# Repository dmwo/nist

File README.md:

# nist
code and other things for nist

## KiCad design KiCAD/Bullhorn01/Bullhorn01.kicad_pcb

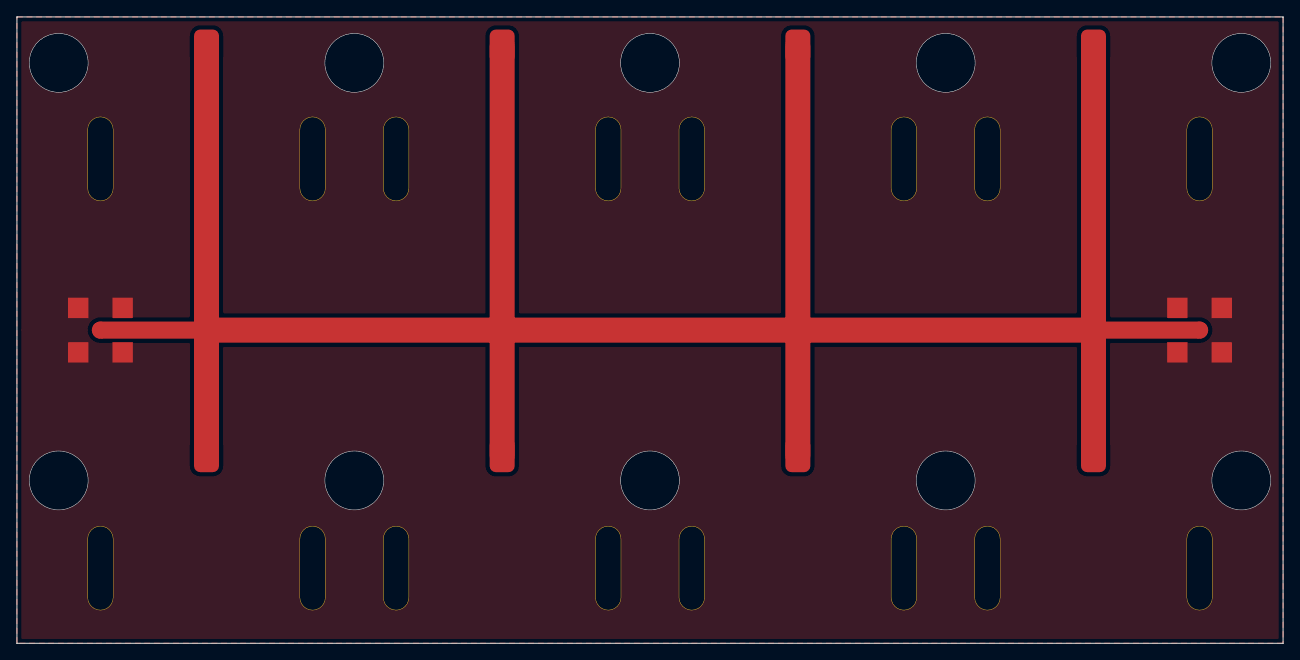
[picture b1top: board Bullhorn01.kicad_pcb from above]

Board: 2 copper layers, 151.6 x 75.0 mm, 10 parts (0 on the bottom side), 2 nets.

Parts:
H1, H2, H3, H4, H5, H6, H7, H8: ZX60-P103LN+
J1, J2: CONSMA001-SMD-G

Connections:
+5V: H1.2, H2.2, H3.2, H4.2, H5.2, H6.2, H7.2, H8.2, J1.1, J2.1
GND: H1.1, H2.1, H3.1, H4.1, H5.1, H6.1, H7.1, H8.1, J1.2, J2.2

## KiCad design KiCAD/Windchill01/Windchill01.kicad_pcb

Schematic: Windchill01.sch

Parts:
C1, C3: 10n; C_0402_1005Metric
C2, C4: 1u; C_0402_1005Metric
D1: LED; LED_0603_1608Metric
G1: Wind_Graphic; wind
J1, J2: C112640
J3: Battery_Holder; 1023
J4: 95278-101A14LF
Q1, Q2: MMBT3904; SOT-23
R1: 1.8k; R_0402_1005Metric
R2: 1M; R_0402_1005Metric
R3: 6.2M; R_0402_1005Metric
R4, R9, R11: 100k; R_0402_1005Metric
R5: 100; R_0402_1005Metric
R6: 10k; R_0402_1005Metric
R7: 499k; R_0402_1005Metric
R8: 180k; R_0402_1005Metric
R10: 80.6k; R_0402_1005Metric
R12: 332; R_0402_1005Metric
R13: 4.02k; R_0402_1005Metric
R14: 102k; R_0402_1005Metric
R15: 3.4k; R_0402_1005Metric
R16: 60.4k; R_0402_1005Metric
R17: 6.8k; R_0402_1005Metric
R18: 13.7k; R_0402_1005Metric
R19: 27.4k; R_0402_1005Metric
U1: AQY221R6V
U2: LTC6702; TSOT-23-8

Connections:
+INA: C4.1, J4.2, J4.4, J4.6, R16.1, U2.3 (+INA)
+INB: C3.1, R6.1, U2.5 (+INB)
-INA: Q2.2 (E), R3.2, R7.1, U2.2 (-INA)
-INB: R2.2, R15.2, R17.2, R18.2, R19.2, U2.6 (-INB)
/1ms: J4.1, R12.1
/10mV: J4.7, R15.1
/10ms: J4.3, R13.1
/20mV: J4.9, R17.1
/40mV: J4.11, R18.1
/80mV: J4.13, R19.1
/100ms: J4.5, R14.1
GND: C1.2, C2.1, C3.2, C4.2, D1.1, J1.2, J2.2, J3.4 (-), J4.8, J4.10, J4.12, J4.14, Q1.2 (E), R7.2, R9.1, R11.2, R16.2, U1.3, U2.4
unnamed: D1.2, R5.1
unnamed: J3.2 (-), J3.3 (+)
unnamed: Q1.1 (B), R4.1
unnamed: Q2.1 (B), R10.1, R11.1
OUTA: R4.2, R5.2, U2.1 (OUTA)
OUTB: R10.2, R12.2, R13.2, R14.2, U2.7 (OUTB)
RELAY+: R1.1, U1.1
RELAY-: Q1.3 (C), U1.2
VDD: C1.1, C2.2, J3.1 (+), R1.2, R2.1, R8.2, U2.8
Vdiv: Q2.3 (C), R3.1, R8.1, R9.2
sig: J1.1, J2.1, R6.2, U1.4

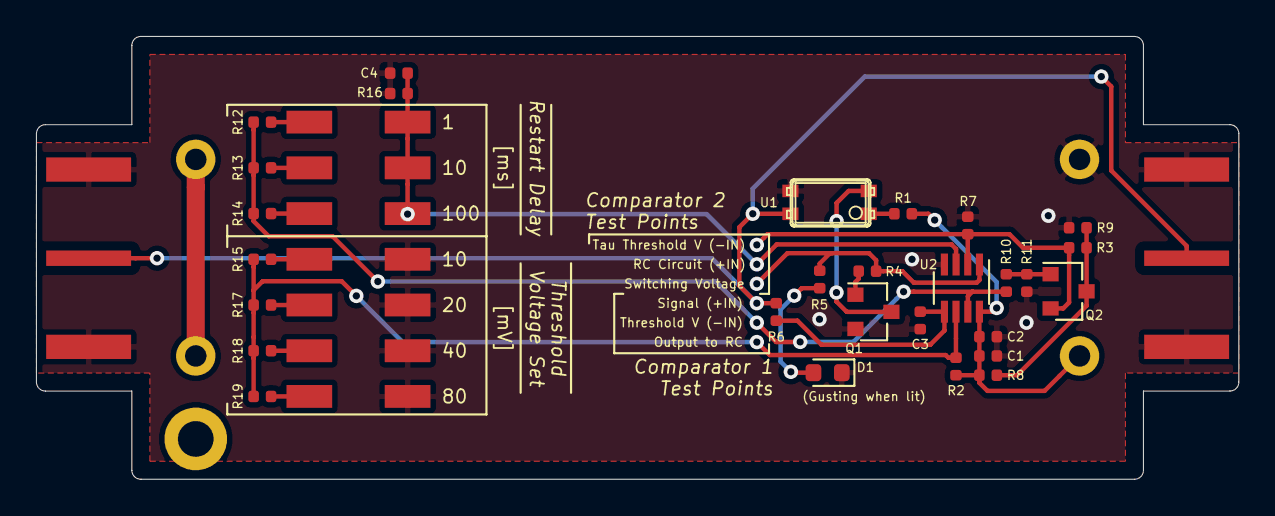
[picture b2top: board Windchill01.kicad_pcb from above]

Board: 2 copper layers, 66.8 x 24.6 mm, 33 parts (1 on the bottom side), 23 nets.

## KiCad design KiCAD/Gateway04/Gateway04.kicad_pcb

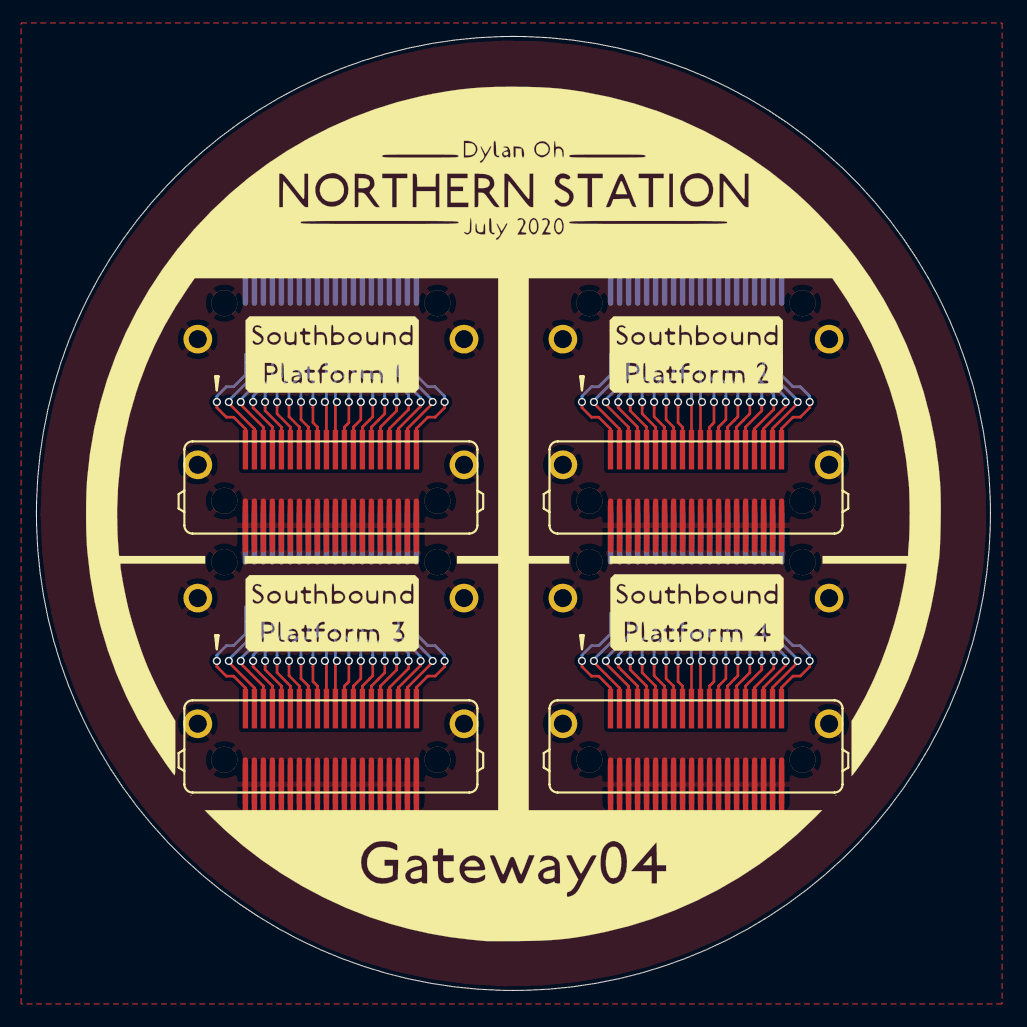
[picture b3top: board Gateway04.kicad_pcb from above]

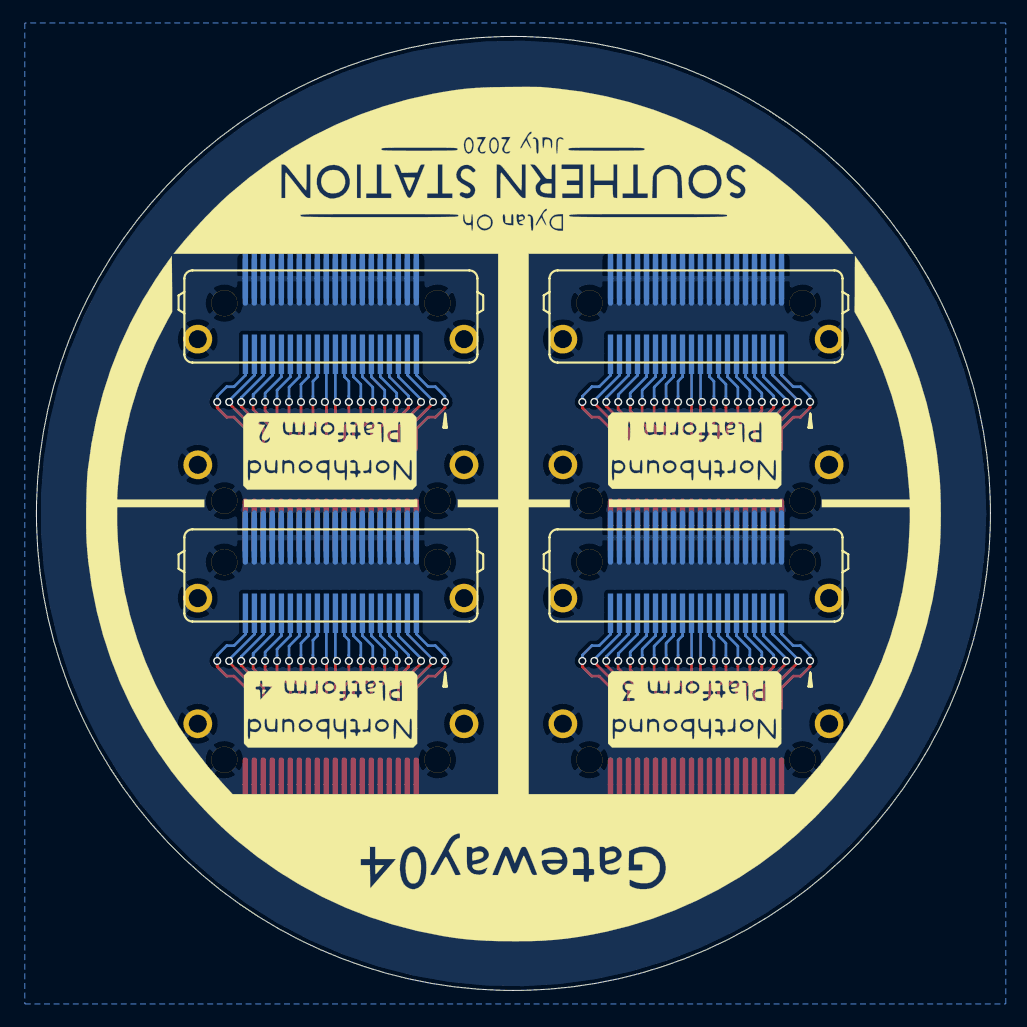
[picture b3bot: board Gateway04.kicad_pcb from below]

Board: 2 copper layers, 53.0 x 53.0 mm, 8 parts (4 on the bottom side), 81 nets.

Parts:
U1, U2, U3, U4, U5, U6, U7, U8: LSHM; LSHM-120-02.5-L-DV-A-S-TR

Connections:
GND: U1.0, U1.1, U1.3, U1.5, U1.7, U1.9, U1.11, U1.13, U1.15, U1.17, U1.19, U1.21, U1.23, U1.25, U1.27, U1.29, U1.31, U1.33, U1.35, U1.37, U1.39, U2.0, U2.1, U2.3, U2.5, U2.7, U2.9, U2.11, U2.13, U2.15, U2.17, U2.19, U2.21, U2.23, U2.25, U2.27, U2.29, U2.31, U2.33, U2.35, U2.37, U2.39, U3.0, U3.1, U3.3, U3.5, U3.7, U3.9, U3.11, U3.13, U3.15, U3.17, U3.19, U3.21, U3.23, U3.25, U3.27, U3.29, U3.31, U3.33, U3.35, U3.37, U3.39, U4.0, U4.1, U4.3, U4.5, U4.7, U4.9, U4.11, U4.13, U4.15, U4.17, U4.19, U4.21, U4.23, U4.25, U4.27, U4.29, U4.31, U4.33, U4.35, U4.37, U4.39, U5.0, U5.1, U5.3, U5.5, U5.7, U5.9, U5.11, U5.13, U5.15, U5.17, U5.19, U5.21, U5.23, U5.25, U5.27, U5.29, U5.31, U5.33, U5.35, U5.37, U5.39, U6.0, U6.1, U6.3, U6.5, U6.7, U6.9, U6.11, U6.13, U6.15, U6.17, U6.19, U6.21, U6.23, U6.25, U6.27, U6.29, U6.31, U6.33, U6.35, U6.37, U6.39, U7.0, U7.1, U7.3, U7.5, U7.7, U7.9, U7.11, U7.13, U7.15, U7.17, U7.19, U7.21, U7.23, U7.25, U7.27, U7.29, U7.31, U7.33, U7.35, U7.37, U7.39, U8.0, U8.1, U8.3, U8.5, U8.7, U8.9, U8.11, U8.13, U8.15, U8.17, U8.19, U8.21, U8.23, U8.25, U8.27, U8.29, U8.31, U8.33, U8.35, U8.37, U8.39
unnamed: U1.2, U2.2
unnamed: U1.4, U2.4
unnamed: U1.6, U2.6
unnamed: U1.8, U2.8
unnamed: U1.10, U2.10
unnamed: U1.12, U2.12
unnamed: U1.14, U2.14
unnamed: U1.16, U2.16
unnamed: U1.18, U2.18
unnamed: U1.20, U2.20
unnamed: U1.22, U2.22
unnamed: U1.24, U2.24
unnamed: U1.26, U2.26
unnamed: U1.28, U2.28
unnamed: U1.30, U2.30
unnamed: U1.32, U2.32
unnamed: U1.34, U2.34
unnamed: U1.36, U2.36
unnamed: U1.38, U2.38
unnamed: U1.40, U2.40
unnamed: U3.2, U4.2
unnamed: U3.4, U4.4
unnamed: U3.6, U4.6
unnamed: U3.8, U4.8
unnamed: U3.10, U4.10
unnamed: U3.12, U4.12
unnamed: U3.14, U4.14
unnamed: U3.16, U4.16
unnamed: U3.18, U4.18
unnamed: U3.20, U4.20
unnamed: U3.22, U4.22
unnamed: U3.24, U4.24
unnamed: U3.26, U4.26
unnamed: U3.28, U4.28
unnamed: U3.30, U4.30
unnamed: U3.32, U4.32
unnamed: U3.34, U4.34
unnamed: U3.36, U4.36
unnamed: U3.38, U4.38
unnamed: U3.40, U4.40
unnamed: U5.2, U6.2
unnamed: U5.4, U6.4
unnamed: U5.6, U6.6
unnamed: U5.8, U6.8
unnamed: U5.10, U6.10
unnamed: U5.12, U6.12
unnamed: U5.14, U6.14
unnamed: U5.16, U6.16
unnamed: U5.18, U6.18
unnamed: U5.20, U6.20
unnamed: U5.22, U6.22
unnamed: U5.24, U6.24
unnamed: U5.26, U6.26
unnamed: U5.28, U6.28
unnamed: U5.30, U6.30
unnamed: U5.32, U6.32
unnamed: U5.34, U6.34
unnamed: U5.36, U6.36
unnamed: U5.38, U6.38
unnamed: U5.40, U6.40
unnamed: U7.2, U8.2
unnamed: U7.4, U8.4
unnamed: U7.6, U8.6
unnamed: U7.8, U8.8
unnamed: U7.10, U8.10
unnamed: U7.12, U8.12
unnamed: U7.14, U8.14
unnamed: U7.16, U8.16
unnamed: U7.18, U8.18
unnamed: U7.20, U8.20
unnamed: U7.22, U8.22
unnamed: U7.24, U8.24
unnamed: U7.26, U8.26
unnamed: U7.28, U8.28
unnamed: U7.30, U8.30
unnamed: U7.32, U8.32
unnamed: U7.34, U8.34
unnamed: U7.36, U8.36
unnamed: U7.38, U8.38
unnamed: U7.40, U8.40

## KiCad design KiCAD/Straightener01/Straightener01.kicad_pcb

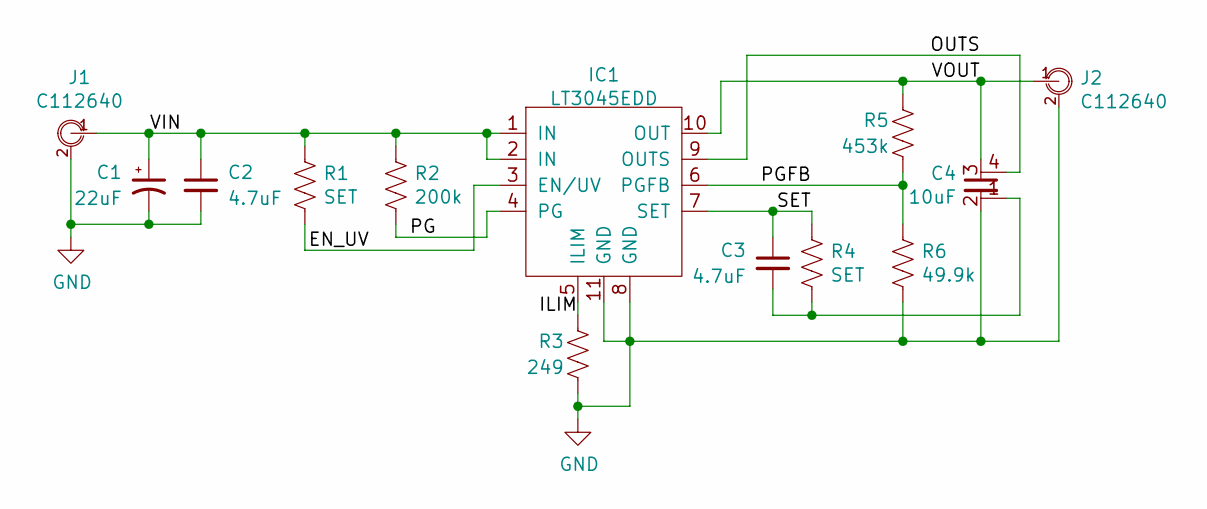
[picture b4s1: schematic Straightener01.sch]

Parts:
C1: 22uF; CP_Elec_5x5.3
C2, C3: 4.7uF; C_1206_3216Metric_Pad1.42x1.75mm_HandSolder
C4: 10uF; C_1206_Split
IC1: LT3045EDD; DFN-10
J1, J2: C112640
R1, R4: SET; R_0603_1608Metric_Pad1.05x0.95mm_HandSolder
R2: 200k; R_0603_1608Metric_Pad1.05x0.95mm_HandSolder
R3: 249; R_0603_1608Metric_Pad1.05x0.95mm_HandSolder
R5: 453k; R_0603_1608Metric_Pad1.05x0.95mm_HandSolder
R6: 49.9k; R_0603_1608Metric_Pad1.05x0.95mm_HandSolder

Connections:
/EN_UV: IC1.3 (EN/UV), R1.2
/ILIM: IC1.5 (ILIM), R3.1
/OUTS: C4.4, IC1.9 (OUTS)
/PG: IC1.4 (PG), R2.2
/PGFB: IC1.6 (PGFB), R5.2, R6.1
/SET: C3.1, IC1.7 (SET), R4.1
/VIN: C1.1, C2.1, IC1.1 (IN), IC1.2 (IN), J1.1, R1.1, R2.1
/VOUT: C4.3, IC1.10 (OUT), J2.1, R5.1
GND: C1.2, C2.2, C4.2, IC1.8 (GND), IC1.11 (GND), J1.2, J2.2, R3.2, R6.2
unnamed: C3.2, C4.1, R4.2

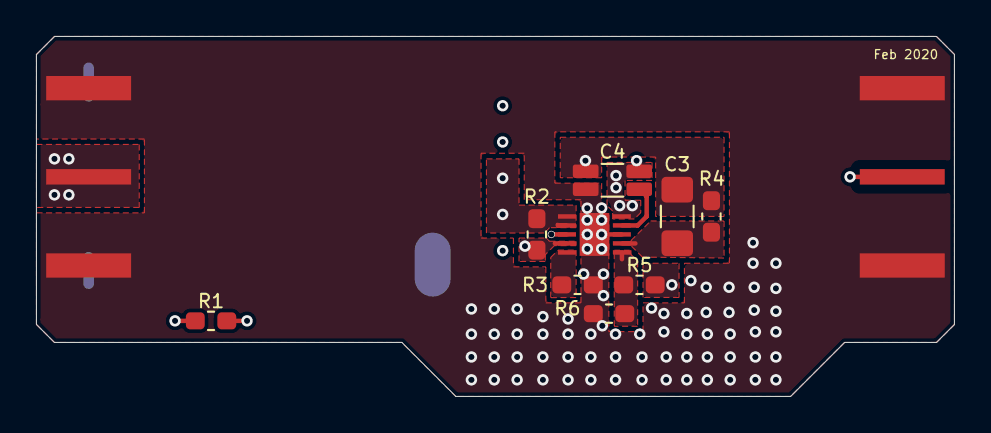
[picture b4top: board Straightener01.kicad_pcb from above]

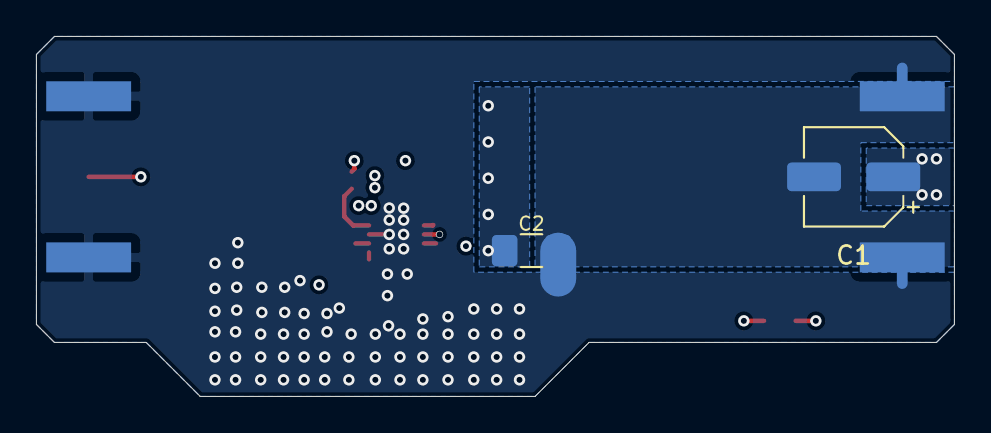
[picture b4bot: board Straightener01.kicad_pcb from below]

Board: 4 copper layers, 51.0 x 20.0 mm, 13 parts (2 on the bottom side), 10 nets.

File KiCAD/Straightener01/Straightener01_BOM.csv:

Item #,Ref Des,Qty,Cost/unit,Manufacturer,Mfg part #,Description,Package,Type,URL
1,C1,1,$0.35 ,Panasonic,EEE-1VA220WR,22uF Pol Cap,"Radial, Can",SMD,https://www.digikey.com/product-detail/en/panasonic-electron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
2,"C2, C3",2,$0.67 ,Murata,GCM31CR71E475KA55L,4.7uF,1206,SMD,https://www.digikey.com/product-detail/en/murata-electronics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
3,C4,1,$1.28 ,Murata,GJ831CR61E106KE83L,10uF,1206,SMD,https://www.digikey.com/product-detail/en/murata-electronics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
4,R2,1,$0.10 ,Vishay,CRCW0603200KJNEA,200 kOhm,0603,SMD,https://www.digikey.com/product-detail/en/vishay-dale/CRCW06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
5,R3,1,$0.10 ,Vishay,CRCW0603249RFKEA,249 Ohm,0603,SMD,https://www.digikey.com/product-detail/en/vishay-dale/CRCW06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
6,R5,1,$0.10 ,Vishay,CRCW0603453KFKEA,453 kOhm,0603,SMD,https://www.digikey.com/product-detail/en/vishay-dale/CRCW06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
7,R6,1,$0.10 ,Vishay,CRCW060349K9FKEA,49.9 kOhm,0603,SMD,https://www.digikey.com/product-detail/en/vishay-dale/CRCW06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
8,"J1, J2",2,$5.72 ,Amphenol,112640,BNC Jack,End Launch,SMD,https://www.digikey.com/product-detail/en/amphenol-rf/112640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
9,IC1,1,$6.78 ,Analog Devices,LT3045EDD#PBF,Regulator,10-DFN,SMD,https://www.digikey.com/product-detail/en/LT3045EDD%23PBF/LT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

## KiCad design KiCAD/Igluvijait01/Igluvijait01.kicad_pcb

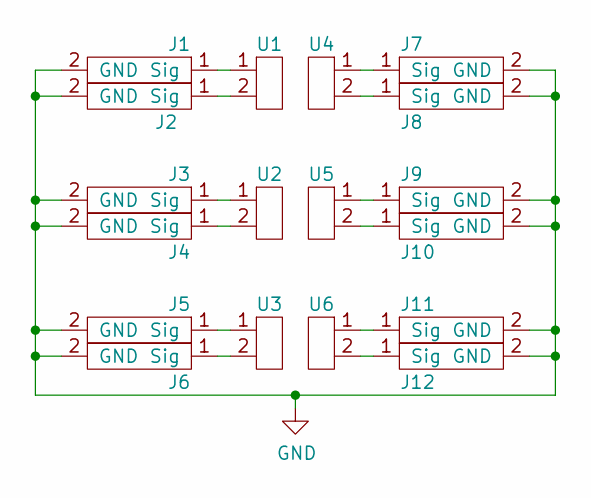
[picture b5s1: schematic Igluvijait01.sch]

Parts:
J1, J2, J3, J4, J5, J6, J7, J8, J9, J10, J11, J12: CONSMA001-SMD-G
U1, U2, U3, U4, U5, U6: TEST_PAD

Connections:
GND: J1.2 (GND), J2.2 (GND), J3.2 (GND), J4.2 (GND), J5.2 (GND), J6.2 (GND), J7.2 (GND), J8.2 (GND), J9.2 (GND), J10.2 (GND), J11.2 (GND), J12.2 (GND)
unnamed: J1.1 (Sig), U1.1
unnamed: J2.1 (Sig), U1.2
unnamed: J3.1 (Sig), U2.1
unnamed: J4.1 (Sig), U2.2
unnamed: J5.1 (Sig), U3.1
unnamed: J6.1 (Sig), U3.2
unnamed: J7.1 (Sig), U4.1
unnamed: J8.1 (Sig), U4.2
unnamed: J9.1 (Sig), U5.1
unnamed: J10.1 (Sig), U5.2
unnamed: J11.1 (Sig), U6.1
unnamed: J12.1 (Sig), U6.2

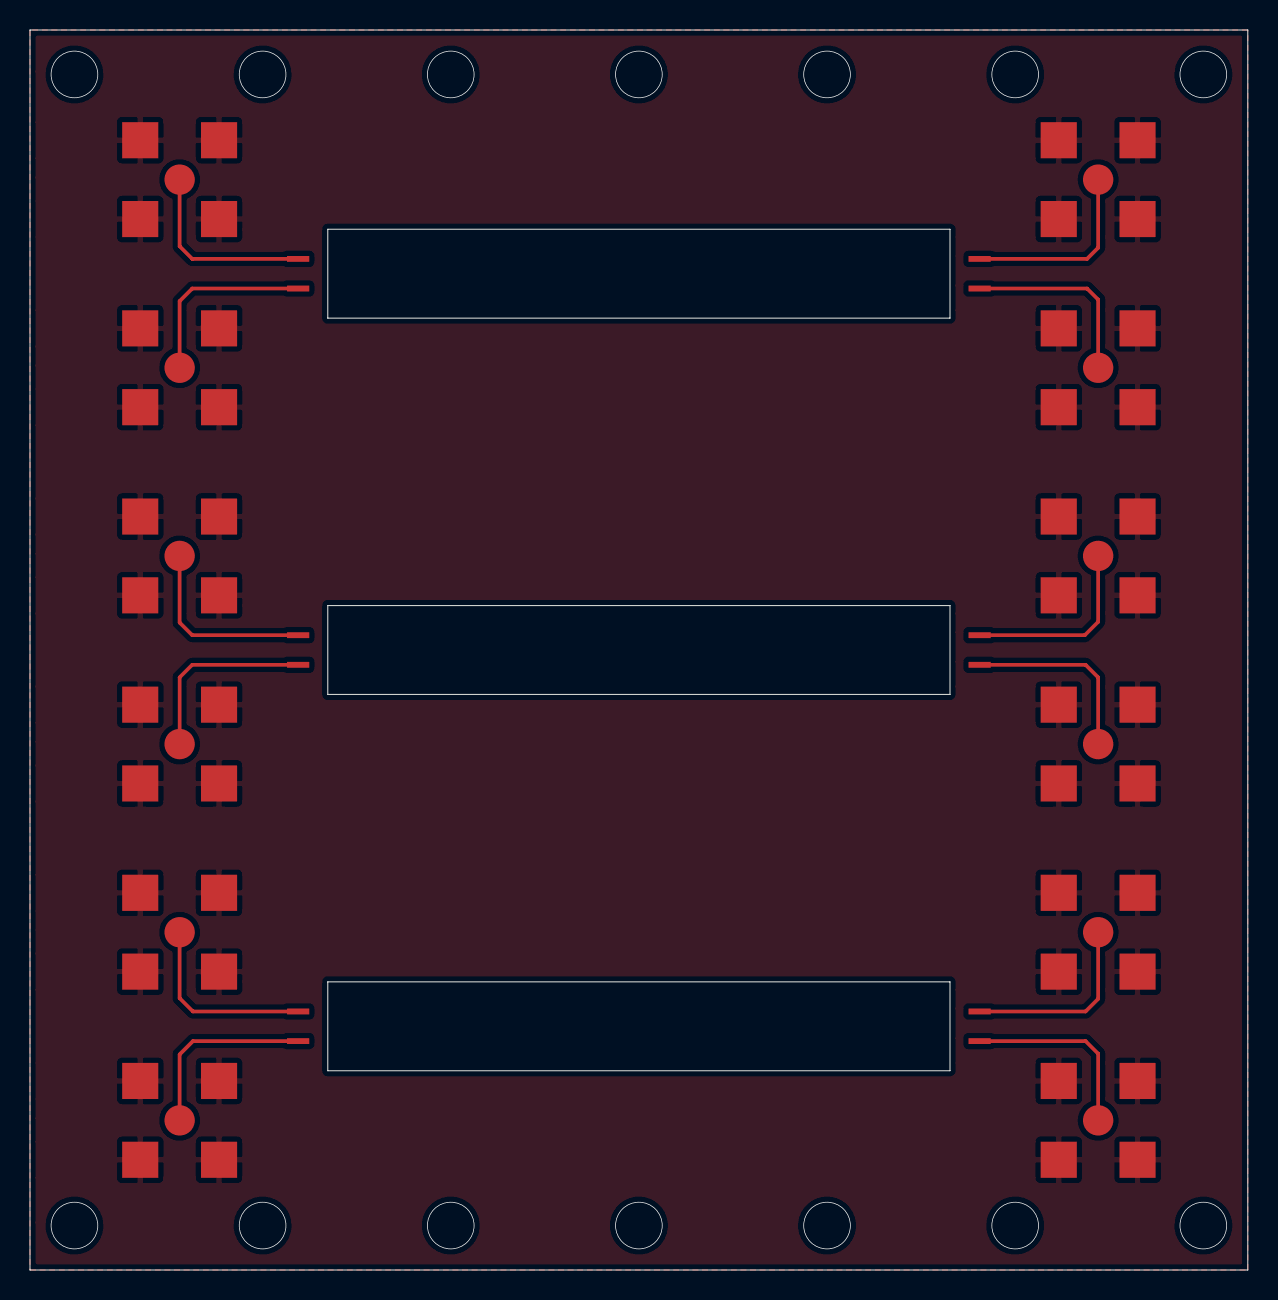
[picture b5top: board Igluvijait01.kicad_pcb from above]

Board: 2 copper layers, 82.2 x 83.7 mm, 18 parts (0 on the bottom side), 13 nets.

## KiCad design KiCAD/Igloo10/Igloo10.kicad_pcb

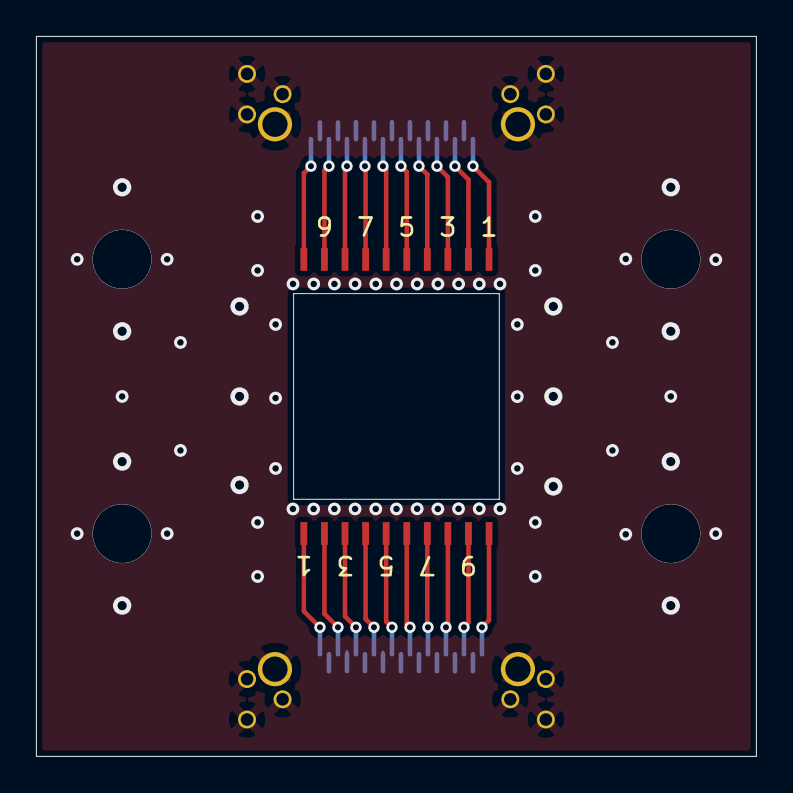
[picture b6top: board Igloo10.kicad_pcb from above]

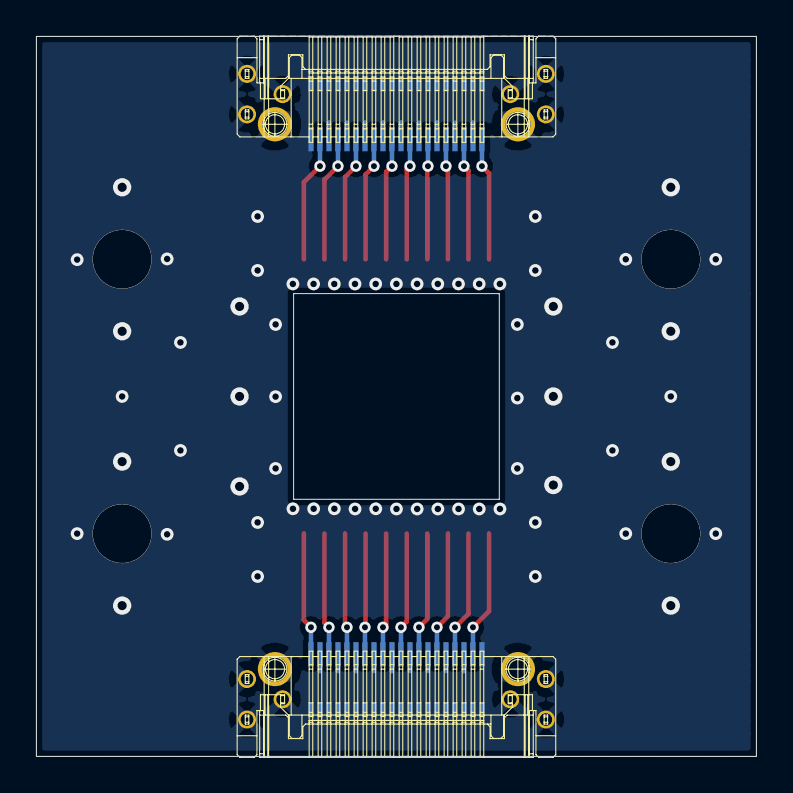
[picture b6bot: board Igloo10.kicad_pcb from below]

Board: 2 copper layers, 40.0 x 40.0 mm, 4 parts (2 on the bottom side), 21 nets.

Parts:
J1, J2: LSHM-120-01-L-RH-A-S-TR; LSHM-110-01-L-RH-A-S-TR
U1, U2: TEST_PAD

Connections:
GND: J1.1, J1.3, J1.4, J1.5, J1.7, J1.8, J1.9, J1.11, J1.12, J1.13, J1.15, J1.16, J1.17, J1.19, J1.20, J1.21, J1.23, J1.24, J1.25, J1.27, J1.28, J1.29, J1.31, J1.32, J1.33, J1.35, J1.36, J1.37, J1.39, J1.40, J1.41, J2.1, J2.3, J2.4, J2.5, J2.7, J2.8, J2.9, J2.11, J2.12, J2.13, J2.15, J2.16, J2.17, J2.19, J2.20, J2.21, J2.23, J2.24, J2.25, J2.27, J2.28, J2.29, J2.31, J2.32, J2.33, J2.35, J2.36, J2.37, J2.39, J2.40, J2.41
unnamed: J1.2, U1.10
unnamed: J1.6, U1.9
unnamed: J1.10, U1.8
unnamed: J1.14, U1.7
unnamed: J1.18, U1.6
unnamed: J1.22, U1.5
unnamed: J1.26, U1.4
unnamed: J1.30, U1.3
unnamed: J1.34, U1.2
unnamed: J1.38, U1.1
unnamed: J2.2, U2.10
unnamed: J2.6, U2.9
unnamed: J2.10, U2.8
unnamed: J2.14, U2.7
unnamed: J2.18, U2.6
unnamed: J2.22, U2.5
unnamed: J2.26, U2.4
unnamed: J2.30, U2.3
unnamed: J2.34, U2.2
unnamed: J2.38, U2.1

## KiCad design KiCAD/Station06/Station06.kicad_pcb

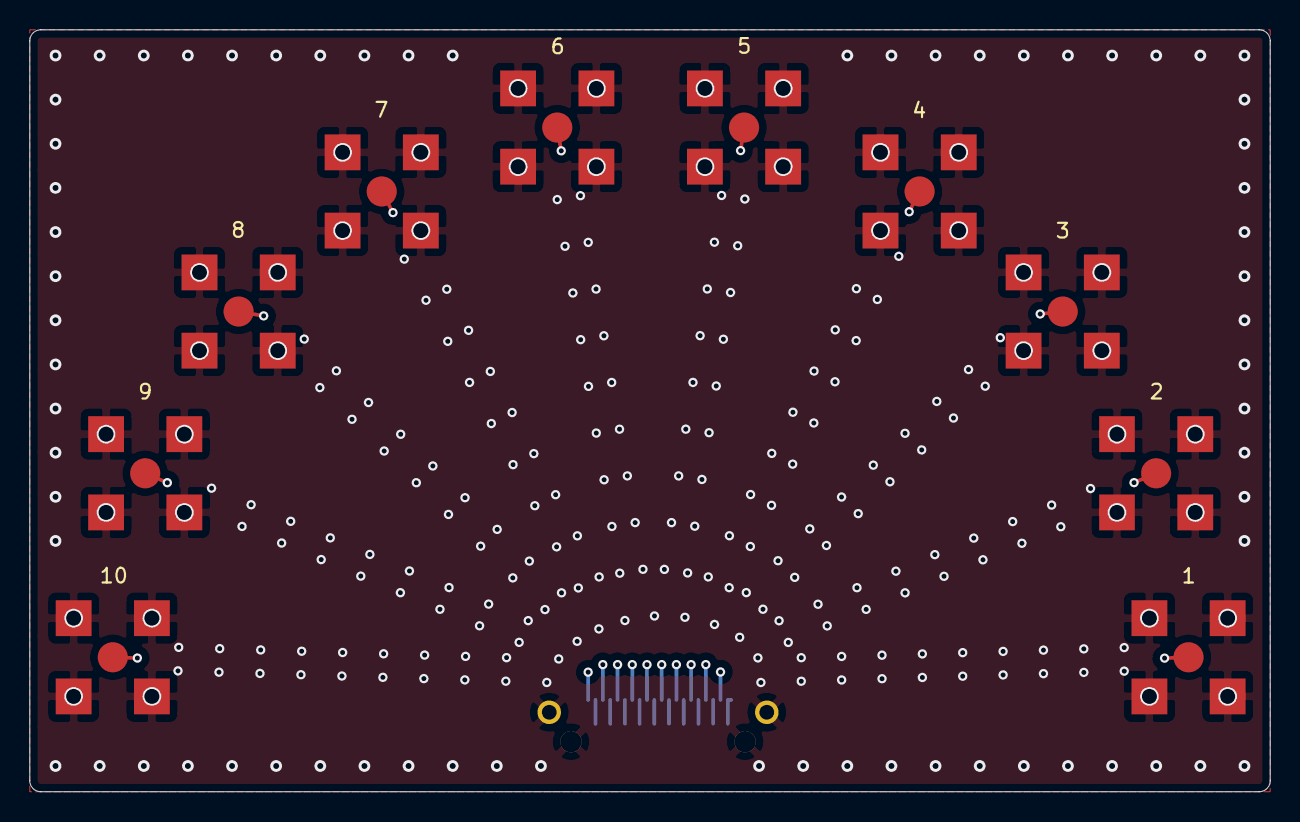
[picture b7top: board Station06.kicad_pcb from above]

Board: 4 copper layers, 84.3 x 51.8 mm, 11 parts (1 on the bottom side), 11 nets.

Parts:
J1: LSHM-120-02.5-L-DV-A-S-TR
J2, J3, J4, J5, J6, J7, J8, J9, J10, J11: CONSMA001-SMD-G

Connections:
GND: J1.0, J1.1, J1.3, J1.4, J1.5, J1.7, J1.8, J1.9, J1.11, J1.12, J1.13, J1.15, J1.16, J1.17, J1.19, J1.20, J1.21, J1.23, J1.24, J1.25, J1.27, J1.28, J1.29, J1.31, J1.32, J1.33, J1.35, J1.36, J1.37, J1.39, J1.40, J2.2, J3.2, J4.2, J5.2, J6.2, J7.2, J8.2, J9.2, J10.2, J11.2
unnamed: J1.2, J11.1
unnamed: J1.6, J10.1
unnamed: J1.10, J9.1
unnamed: J1.14, J8.1
unnamed: J1.18, J7.1
unnamed: J1.22, J6.1
unnamed: J1.26, J5.1
unnamed: J1.30, J4.1
unnamed: J1.34, J3.1
unnamed: J1.38, J2.1

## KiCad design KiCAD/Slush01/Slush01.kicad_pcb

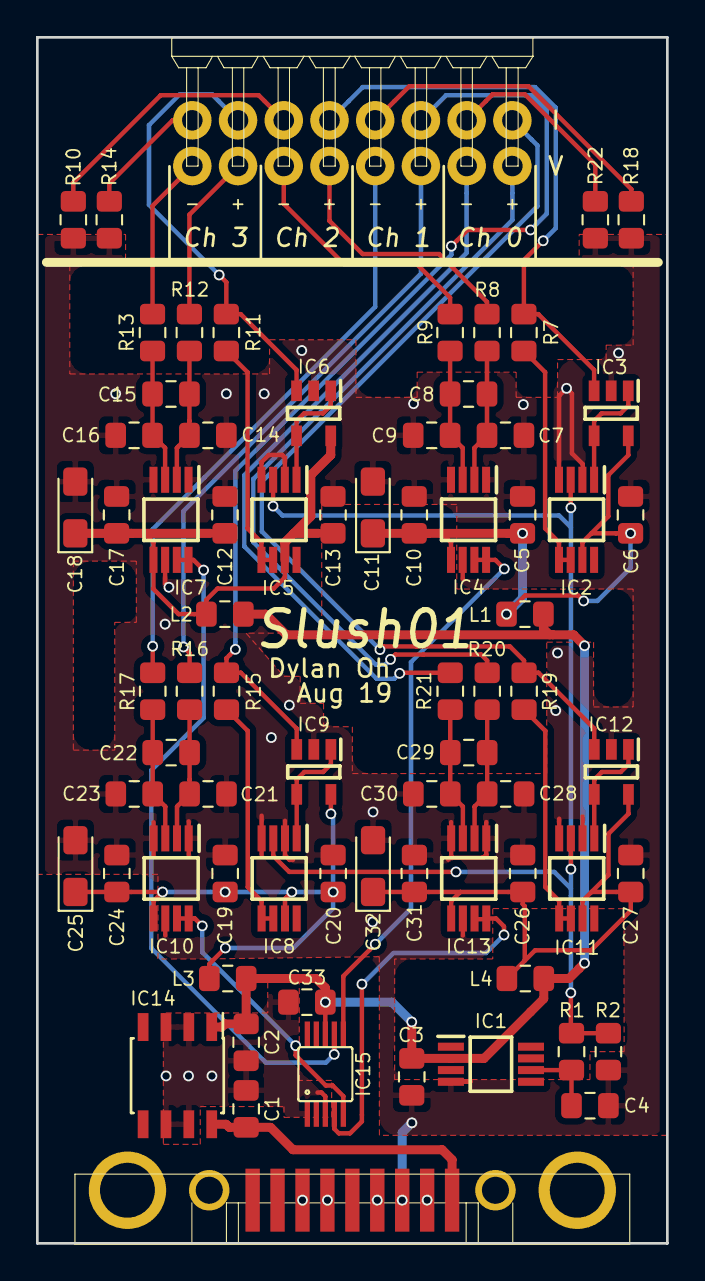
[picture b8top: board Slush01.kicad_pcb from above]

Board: 2 copper layers, 35.0 x 67.0 mm, 72 parts (0 on the bottom side), 48 nets.

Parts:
C1: 0.33uF; C_0805_2012Metric_Pad1.15x1.40mm_HandSolder
C2: 0.01uF; C_0805_2012Metric_Pad1.15x1.40mm_HandSolder
C3, C4, C5, C6, C7, C9, C10, C12, C13, C14, C16, C17, C19, C20, C21, C23, C24, C26, C27, C28, C30, C31, C33: 0.1uF; C_0805_2012Metric_Pad1.15x1.40mm_HandSolder
C8, C15, C22, C29: 1uF 6.3V X7R 0805; C_0805_2012Metric_Pad1.15x1.40mm_HandSolder
C11, C18, C25, C32: 10uF; CP_EIA-3216-18_Kemet-A_Pad1.58x1.35mm_HandSolder
IC1: ADR440ARMZ; MSOP-8
IC2, IC5, IC8, IC11: AD8276ARMZ; MSOP-8
IC3, IC6, IC9, IC12: AD8603AUJZ-R2; TSOT-23-5
IC4, IC7, IC10, IC13: AD8237ARMZ; MSOP-8
IC14: LM78L05; SOIC-8
IC15: ADS1115; VSSOP-10
J1: DB9F; K202XHT-E9S-N
J2: 90122-0128
L1, L2, L3, L4: MMZ2012Y152B; L_0805_2012Metric_Pad1.15x1.40mm_HandSolder
R1: 1050; R_0805_2012Metric_Pad1.15x1.40mm_HandSolder
R2: 1K; R_0805_2012Metric_Pad1.15x1.40mm_HandSolder
R7, R8, R9, R11, R12, R13, R15, R16, R17, R19, R20, R21: 100k; R_0805_2012Metric_Pad1.15x1.40mm_HandSolder
R10, R14, R18, R22: 10k; R_0805_2012Metric_Pad1.15x1.40mm_HandSolder

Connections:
/1V: IC2.3, IC5.3, IC8.3, IC11.3, R1.2, R2.1
/Channel0/I+: IC12.3, J2.2, R19.2
/Channel0/I-: J2.4, R22.1
/Channel0/V+: J2.1, R20.2
/Channel0/V-: J2.3, R21.2
/Channel0/Vpower: C26.1, C27.1, C31.1, C32.1, IC11.7, IC12.5, IC13.5, L4.2
/Channel0/out: IC13.7, IC13.8, IC15.4
/Channel1/I+: IC9.3, J2.6, R15.2
/Channel1/I-: J2.8, R18.1
/Channel1/V+: J2.5, R16.2
/Channel1/V-: J2.7, R17.2
/Channel1/Vpower: C19.1, C20.1, C24.1, C25.1, IC8.7, IC9.5, IC10.5, L3.2
/Channel1/out: IC10.7, IC10.8, IC15.5
/Channel2/I+: IC3.3, J2.10, R7.2
/Channel2/I-: J2.12, R10.1
/Channel2/V+: J2.9, R8.2
/Channel2/V-: J2.11, R9.2
/Channel2/Vpower: C5.1, C6.1, C10.1, C11.1, IC2.7, IC3.5, IC4.5, L1.2
/Channel2/out: IC4.7, IC4.8, IC15.6
/Channel3/I+: IC6.3, J2.14, R11.2
/Channel3/I-: J2.16, R14.1
/Channel3/V+: J2.13, R12.2
/Channel3/V-: J2.15, R13.2
/Channel3/Vpower: C12.1, C13.1, C17.1, C18.1, IC5.7, IC6.5, IC7.5, L2.2
/Channel3/out: IC7.7, IC7.8, IC15.7
/Power: C2.1, C3.1, C33.2, IC1.2, IC14.1, IC15.8, L1.1, L2.1, L3.1, L4.1
GND: C1.2, C2.2, C33.1, IC14.2, IC14.3, IC14.6, IC14.7, IC15.1, IC15.3, J1.2, J1.7, J1.8, J1.9, J1.10
GNDA: C3.2, C4.2, C5.2, C6.2, C7.1, C9.2, C10.2, C11.2, C12.2, C13.2, C14.1, C16.2, C17.2, C18.2, C19.2, C20.2, C21.1, C23.2, C24.2, C25.2, C26.2, C27.2, C28.1, C30.2, C31.2, C32.2, IC1.4, IC2.2, IC2.4, IC3.2, IC4.1, IC4.4, IC4.6, IC5.2, IC5.4, IC6.2, IC7.1, IC7.4, IC7.6, IC8.2, IC8.4, IC9.2, IC10.1, IC10.4, IC10.6, IC11.2, IC11.4, IC12.2, IC13.1, IC13.4, IC13.6, J1.4, R2.2, R10.2, R14.2, R18.2, R22.2
unnamed: C1.1, IC14.8, J1.5
unnamed: C4.1, IC1.6, R1.1
unnamed: C7.2, C8.1, IC4.2, R8.1
unnamed: C8.2, C9.1, IC4.3, R9.1
unnamed: C14.2, C15.1, IC7.2, R12.1
unnamed: C15.2, C16.1, IC7.3, R13.1
unnamed: C21.2, C22.1, IC10.2, R16.1
unnamed: C22.2, C23.1, IC10.3, R17.1
unnamed: C28.2, C29.1, IC13.2, R20.1
unnamed: C29.2, C30.1, IC13.3, R21.1
unnamed: IC2.1, IC3.1, IC3.4
unnamed: IC2.5, IC2.6, R7.1
unnamed: IC5.1, IC6.1, IC6.4
unnamed: IC5.5, IC5.6, R11.1
unnamed: IC8.1, IC9.1, IC9.4
unnamed: IC8.5, IC8.6, R15.1
unnamed: IC11.1, IC12.1, IC12.4
unnamed: IC11.5, IC11.6, R19.1
SCL: IC15.10, J1.6
SDA: IC15.9, J1.1

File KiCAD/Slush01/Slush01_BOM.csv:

Item #,Ref Des,Qty [individual part],Cost per unit,Manufacturer,Mfg part #,Description/Value,Package,Type,Notes,Website URL
1,C1,1,0.28,Yageo,CC0805JKX7R7BB334,0.33uF,0805 (2012 Metric),SMD,,https://www.digikey.com/product-detail/en/yageo/CC0805JKX7R7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
2,C2,1,0.15,Yageo,CC0805JRX7R9BB103,0.01uF,0805 (2012 Metric),SMD,,https://www.digikey.com/product-detail/en/yageo/CC0805JRX7R9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
3,"C8,C15,C22,C29",4,0.17,Yageo,CC0805KKX7R8BB105,1uF,0805 (2012 Metric),SMD,,https://www.digikey.com/product-detail/en/yageo/CC0805KKX7R8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
4,"C11,C18,C25,C32",4,0.48,AVX Corp,F930J106KAA,10uF Tantalum,1206 (3216 Metric),SMD,,https://www.digikey.com/product-detail/en/avx-corporation/F9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
5,"C3,C4,C5,C6,C7,C9,C10,C12,C13,C14,C16,C17,C19,C20,C21,C23,C24,C26,C27,C28,C30,C31,C33",23,0.087,Yageo,CC0805KRX7R9BB104,0.1uF,0805 (2012 Metric),SMD,,https://www.digikey.com/product-detail/en/yageo/CC0805KRX7R9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
6,"L1,L2,L3,L4",4,0.11,TDK Corp,MMZ2012Y152BTD25,Ferrite Bead 1.5k?,0805 (2012 Metric),SMD,,https://www.digikey.com/product-detail/en/tdk-corporation/MM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
7,R1,1,0.1,Yageo,RC0805FR-071K05L,1.05k,0805 (2012 Metric),SMD,,https://www.digikey.com/product-detail/en/yageo/RC0805FR-071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
8,R2,1,0.1,Yageo,RT0805FRE071KL,1k,0805 (2012 Metric),SMD,,https://www.digikey.com/product-detail/en/yageo/RT0805FRE071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
9,"R10,R14,R18,R22",4,0.14,Yageo,RT0805DRE0710KL,10k,0805 (2012 Metric),SMD,,https://www.digikey.com/product-detail/en/yageo/RT0805DRE071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
10,"R7,R8,R9,R11,R12,R13,R15,R16,R17,R19,R20,R21",12,0.127,Yageo,RT0805DRE07100KL,100k,0805 (2012 Metric),SMD,,https://www.digikey.com/product-detail/en/yageo/RT0805DRE071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
11,J1,1,3.98,Kycon,K202XHT-E9S-N,DB9 Serial Connector Female,K202XHT-E9S-N,SMD/THM,,https://www.digikey.com/product-detail/en/kycon-inc/K202XHT-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
12,J2,1,2.46,Molex,901220128,Connector Header Right Angle 16 pos,901220128,THM,,https://www.digikey.com/product-detail/en/molex/0901220128/W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
13,IC1,1,7.64,Analog Devices,ADR440ARMZ,V Ref IC,MSOP-8,SMD,,https://www.digikey.com/product-detail/en/analog-devices-inc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
14,IC14,1,0.69,Texas Instruments,LM78L05ACMX/NOPB,LM78L05 Linear Regulator,SOIC-8,SMD,,https://www.digikey.com/product-detail/en/texas-instruments/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
15,IC15,1,6.35,Texas Instruments,ADS1115IDGST,16-bit ADC,VSSOP-10,SMD,,https://www.digikey.com/product-detail/en/texas-instruments/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
16,"IC2,IC5,IC8,IC11",4,2.73,Analog Devices,AD8276ARMZ-RL,Differential Op Amp,MSOP-8,SMD,,https://www.digikey.com/product-detail/en/analog-devices-inc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
17,"IC3,IC6,IC9,IC12",4,2.73,Analog Devices,AD8603AUJZ-R2,Op Amp,TSOT-23-5,SMD,,https://www.digikey.com/product-detail/en/analog-devices-inc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
18,"IC4,IC7,IC10,IC13",4,2.7,Analog Devices,AD8237ARMZ,Instrumentation Amplifier,MSOP-8,SMD,,https://www.digikey.com/product-detail/en/analog-devices-inc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

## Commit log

2019-02-08 added jeol contents
2019-02-08 added snspd_measure
2019-02-08 added diptrace_pcbs
2019-02-14 added small world folder
2019-02-28 added igloo08
2019-02-28 added all known files
2019-03-12 small change on small world
2019-03-14 fixed micro d connector spacing issue in igloo08
2019-04-12 added north/south indicators to igloo08
2019-04-23 added test
2019-04-23 added kicad folder
2019-04-23 moved test files into kicad
2019-04-24 added feedthrough pcb files
2019-04-24 organised files
2019-04-24 updated feedthrough pcb
2019-04-24 added miscellaneous folder
2019-04-30 added igloo06
2019-05-02 more work on igloo06
2019-05-03 finalised Igloo09
2019-06-21 reorganised and added station04/05
2019-06-21 added o ring
2019-06-24 finished station04 and station05
2019-06-25 Fixed some issues in Station PCBs
2019-06-26 added 3d models to feedthrough_pcb
2019-06-26 finished 260619 presentation
2019-06-26 added 3d models to Station05
2019-06-26 started a compendium of fake email accounts
2019-07-01 added pnp interface python code
2019-07-01 removed some things
2019-07-03 added code for interfacing with the spectrum analyser
2019-07-03 small changes
2019-07-16 removed feedthrough_pcb from KiCAD folder
2019-07-16 finished Gateway01 PCB
2019-07-17 added 3d models to Igloo09
2019-07-17 added solidworks rendering of feedthrough pcb
2019-07-17 minor changes to Station05
2019-07-17 minor changes to pnp_interface
2019-08-01 added new account for 3dcontentcentral
2019-08-01 finished current source
2019-08-01 removed unnecessary files from Gateway01
2019-08-01 renamed Current_Source to Slush01 and added BOM
2019-08-01 finalised Slush01
2019-08-02 added ADC to Slush01
2019-08-02 exposed vias and fixed thermals on Gateway01
2019-08-12 added LTSpice simulation schematic for Windchill01
2019-08-12 added Windchill01 KiCAD files
2019-08-12 added 3d models for Windchill01 parts
2019-08-15 removed obsolete files from Windchill01
2019-08-15 fixed covered test vias on Station05
2019-08-15 Update fp-info-cache
2019-08-15 added Windchill01 simulation data and code
2019-08-15 updated 3d models, added wind graphic
2019-08-15 added Windchill01 BOM
2019-08-15 added pick and place position file for Windchill01
2019-08-15 finished Windchill01
2019-08-16 added gerber files
2019-08-19 readded wind graphic
2019-08-19 finished Windchill01 for real this time
2019-08-19 added dimensions to Windchill01
2019-08-22 added Station05 network analyser measurements
2019-09-04 added Slush01 interfacing code
2019-09-23 started Slush02
2019-10-10 created Gateway02
2019-10-10 more routing work on Slush02
    moved ground plane to bottom layer
2019-11-25 created Gateway03
2019-11-25 finished Gateway03
2019-11-25 created Station06
2019-12-19 more work on Station06
2020-01-02 fixed via spacing issue on Gateway03
2020-01-16 finished Station06
2020-01-16 created Igloo10
2020-01-16 added via border to Station06 and finalised
2020-01-17 finished Igloo10
2020-01-31 created and finished draft of Igluvijait01
2020-01-31 created Straightener01, finished schematic
2020-02-12 fixed ground connectivity on Slush02
2020-02-12 more plane work on Straightener01
2020-02-28 finished up Straightener01
2020-02-29 added Gateway04
2020-02-29 finished Gateway04
2020-07-21 added euler curve code
2020-07-21 created gateway04
2020-07-21 finished euler curve function
2020-07-22 finished Gateway04, added silkscreen
2020-07-23 fixed curvature function, need to fix Reff
2020-07-24 finished curve_array
2020-07-24 changed curve_array to partial_euler
2020-08-14 changed partial_euler to work off Rmin
2020-08-15 spiral works, no same port side, disconts
2020-08-15 spiral-to-stub discont fixed, same side port fixed
2020-08-17 fixed partial_euler
2020-08-21 Finish tanh centre arc implementation, some errors
2020-09-30 Finished SMA Tester
